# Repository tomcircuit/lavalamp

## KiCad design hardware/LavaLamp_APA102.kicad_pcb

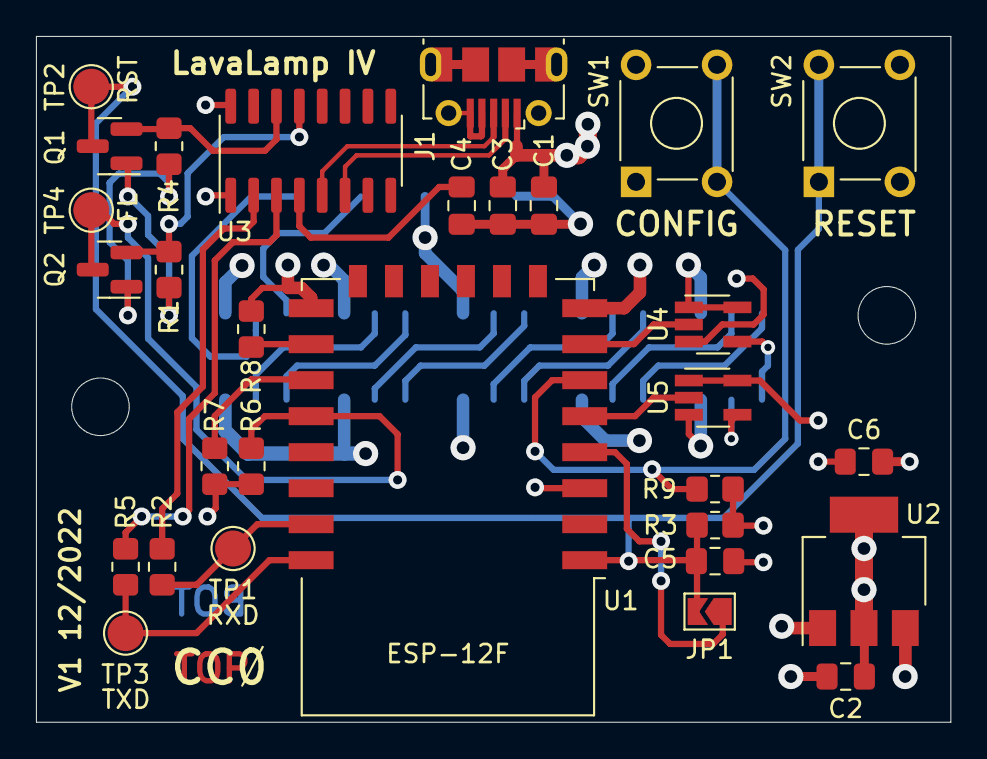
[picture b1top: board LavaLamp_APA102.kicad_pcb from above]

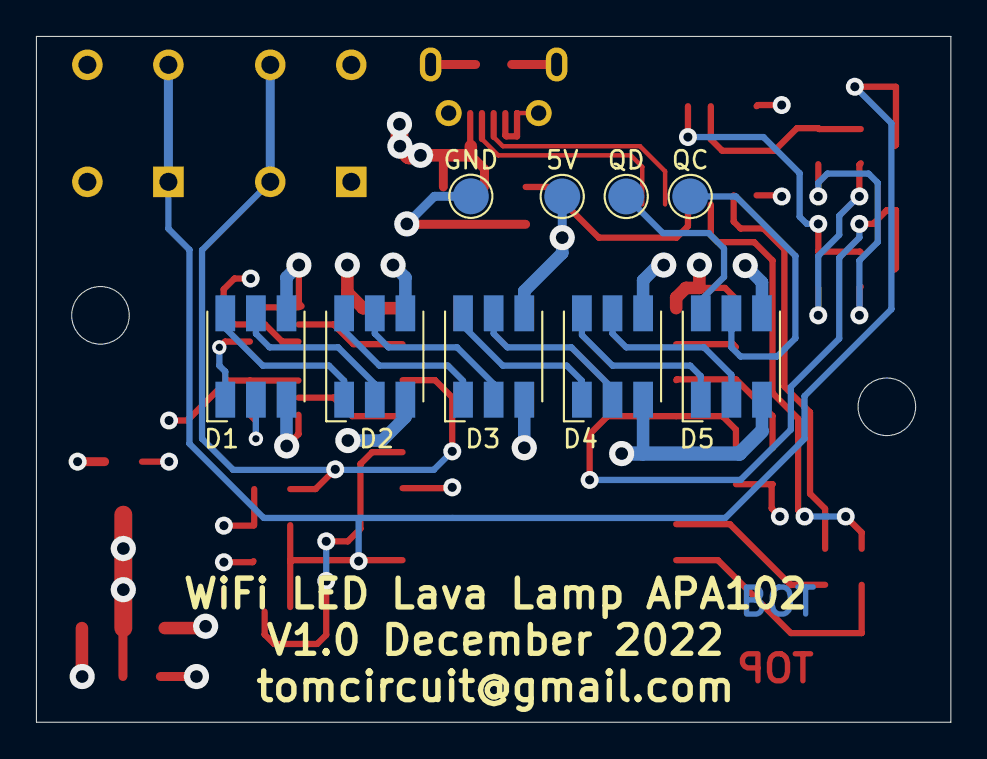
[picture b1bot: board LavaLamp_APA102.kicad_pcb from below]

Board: 4 copper layers, 50.8 x 38.1 mm, 41 parts (9 on the bottom side), 34 nets.

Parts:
C1, C2: 4.7uF; C_0805_2012Metric_Pad1.18x1.45mm_HandSolder
C3, C4, C6: 100nF; C_0805_2012Metric_Pad1.18x1.45mm_HandSolder
C5: 470pF; C_0805_2012Metric_Pad1.18x1.45mm_HandSolder
D1, D2, D3, D4, D5: APA102; LED_RGB_5050-6
H1, H2: 0.125in hole; MountingHole_3.2mm_M3
J1: USB_B_Micro; USB_Micro-B_Molex-105017-0001
JP1: Jumper_2_Open; SolderJumper-2_P1.3mm_Open_TrianglePad1.0x1.5mm
Q1, Q2: MMBTA06; SOT-23
R1, R3, R4, R6, R7, R8, R9: 10K; R_0805_2012Metric_Pad1.20x1.40mm_HandSolder
R2, R5: 470; R_0805_2012Metric_Pad1.20x1.40mm_HandSolder
SW1, SW2: SW_Push_Dual; SW_TH_Tactile_Omron_B3F-10xx
TP1: RXD; TestPoint_Pad_D2.0mm
TP2: RST; TestPoint_Pad_D2.0mm
TP3: TXD; TestPoint_Pad_D2.0mm
TP4: GPIO0; TestPoint_Pad_D2.0mm
TP5: QD; TestPoint_Pad_D2.0mm
TP6: QC; TestPoint_Pad_D2.0mm
TP7: GND; TestPoint_Pad_D2.0mm
TP8: 5V; TestPoint_Pad_D2.0mm
U1: ESP-12F; ESP-12E
U2: LM1117-3.3; SOT-223-3_TabPin2
U3: CH340C; SOIC-16_3.9x9.9mm_P1.27mm
U4, U5: 74AHCT1G126; SOT-23-5_HandSoldering

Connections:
+5V: C1.1, C3.1, C6.1, D1.4 (VCC), D2.4 (VCC), D3.4 (VCC), D4.4 (VCC), D5.4 (VCC), J1.1 (VBUS), TP8.1, U2.3 (VI), U3.16 (VCC), U4.1, U4.5 (VCC), U5.1, U5.5 (VCC)
/DTR: Q2.2 (E), R1.1, U3.13 (~DTR)
/GPIO0: Q2.3 (C), R6.1, TP4.1, U1.18 (GPIO0)
/GPIO2: R7.2, U1.17 (GPIO2)
/GPIO12: R9.2, SW1.2, U1.6 (GPIO12)
/GPIO13: U1.7 (GPIO13), U4.2
/GPIO14: U1.5 (GPIO14), U5.2
/GPIO15: R8.2, U1.16 (GPIO15)
/MOSI: D1.1 (DI), U4.4
/RST: C5.1, JP1.2 (B), Q1.3 (C), R3.1, SW2.1, TP2.1, U1.1 (~RST)
/RTS: Q1.2 (E), R4.1, U3.14 (~RTS)
/RXD0: R2.2, TP1.1, U1.21 (GPIO3/RXD)
/SCLK: D1.2 (CI), U5.4
/TXD0: R5.2, TP3.1, U1.22 (GPIO1/TXD)
/USBRX: R5.1, U3.3 (RXD)
/USBTX: R2.1, U3.2 (TXD)
/WAKE: JP1.1 (A), U1.4 (GPIO16)
GND: C1.2, C2.2, C3.2, C4.2, C5.2, C6.2, D1.3 (GND), D2.3 (GND), D3.3 (GND), D4.3 (GND), D5.3 (GND), J1.4 (ID), J1.5 (GND), J1.6 (Shield), R8.1, SW1.1, SW2.2, TP7.1, U1.15 (GND), U2.1 (GND), U3.1 (GND), U4.3 (GND), U5.3 (GND)
unnamed: C4.1, U3.4 (V3)
unnamed: D1.5 (CO), D2.2 (CI)
unnamed: D1.6 (DO), D2.1 (DI)
unnamed: D2.5 (CO), D3.2 (CI)
unnamed: D2.6 (DO), D3.1 (DI)
unnamed: D3.5 (CO), D4.2 (CI)
unnamed: D3.6 (DO), D4.1 (DI)
unnamed: D4.5 (CO), D5.2 (CI)
unnamed: D4.6 (DO), D5.1 (DI)
unnamed: D5.5 (CO), TP6.1
unnamed: D5.6 (DO), TP5.1
unnamed: J1.2 (D-), U3.6 (UD-)
unnamed: J1.3 (D+), U3.5 (UD+)
unnamed: Q1.1 (B), R1.2
unnamed: Q2.1 (B), R4.2
VDD: C2.1, R3.2, R6.2, R7.1, R9.1, U1.3 (EN), U1.8 (VCC), U2.2 (VO)

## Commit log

2024-05-30 Initial commit
    V1 PCB post-final assembly into wooden box.

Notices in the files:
hardware/LavaLamp_APA102.kicad_pcb:
CC0
